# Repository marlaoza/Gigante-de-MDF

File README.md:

```
      _,---.   .=-.-.    _,---.   ,---.      .-._        ,--.--------.    ,----.  
  _.='.'-,  \ /==/_ /_.='.'-,  \.--.'  \    /==/ \  .-._/==/,  -   , -\,-.--` , \ 
 /==.'-     /|==|, |/==.'-     /\==\-/\ \   |==|, \/ /, |==\.-.  - ,-./==|-  _.-` 
/==/ -   .-' |==|  /==/ -   .-' /==/-|_\ |  |==|-  \|  | `--`\==\- \  |==|   `.-. 
|==|_   /_,-.|==|- |==|_   /_,-.\==\,   - \ |==| ,  | -|      \==\_ \/==/_ ,    / 
|==|  , \_.' )==| ,|==|  , \_.' )==/ -   ,| |==| -   _ |      |==|- ||==|    .-'  
\==\-  ,    (|==|- \==\-  ,    (==/-  /\ - \|==|  /\ , |      |==|, ||==|_  ,`-._ 
 /==/ _  ,  //==/. //==/ _  ,  |==\ _.\=\.-'/==/, | |- |      /==/ -//==/ ,     / 
 `--`------' `--`-` `--`------' `--`        `--`./  `--`      `--`--``--`-----``

                     ,----.                ___                  _,---.  
      _,..---._   ,-.--` , \        .-._ .'=.'\  _,..---._   .-`.' ,  \ 
    /==/,   -  \ |==|-  _.-`       /==/ \|==|  /==/,   -  \ /==/_  _.-' 
    |==|   _   _\|==|   `.-.       |==|,|  / - |==|   _   _Y==/-  '..-. 
    |==|  .=.   /==/_ ,    /       |==|  \/  , |==|  .=.   |==|_ ,    / 
    |==|,|   | -|==|    .-'        |==|- ,   _ |==|,|   | -|==|   .--'  
    |==|  '='   /==|_  ,`-._       |==| _ /\   |==|  '='   /==|-  |     
    |==|-,   _`//==/ ,     /       /==/  / / , /==|-,   _`//==/   \     
    `-.`.____.' `--`-----``        `--`./  `--``-.`.____.' `--`---'     
```

O **Gigante de MDF** é um carrinho de batalha controlado por comandos serial via **Bluetooth**, interpretados pelo USART do microcontrolador **ATmega328P**.  

O projeto inclui:
- Dois motores DC 5V controlados por um C.I L298N (movimentação)
- Um sensor **LDR** (detecção de acerto de laser)  
- Um **display de 7 segmentos** (contador de vidas)  
- Um **laser 5 V** (arma)
- Um módulo bluetooth HC-10 (controle)

## Descrição De Recursos

Todas as funcionalidades do carrinho são controladas via bytes enviados pelo HC-10.
Os comandos aceitos são:
| Comando | Ação |
|---------|------|
| `f` | Move o carrinho para frente |
| `b` | Move o carrinho para trás |
| `l` | Vira o carrinho para esquerda |
| `r` | Vira o carrinho para direita |
| `p` | Para os motores |
| `m` | Troca o modo do laser para manual |
| `a` | Troca o modo do laser para automático |
| `s` | Dispara laser (no modo manual) |
| `0` | Girar 180° |
| `1` | Impulso para frente |
| `3` | Reseta vidas |
| `!` | Alterna o modo de depuração |
| `+` / `-` | Ajusta velocidade |
| `h` | Mostra os comandos |

Os motores são controlados pelo C.I de ponte H L298N, com a velocidade sendo modulada via PWM
Cada um dos motores tem um Timer diferente (*Timer0* e *Timer1*) controlando sua saida PWM.

O laser possui dois modos de operação:

### • Modo Automático  
Liga e desliga a cada 1 segundo.

### • Modo Manual  
Controlado por comando Bluetooth.  
Quando ativado, dispara por 1 segundo e entra em *cooldown* por mais 1 segundo.

O tempo do timer é controlado pelo *Timer2* do **Atmega328P** utilizando a interrupção de overflow para contar até 1 segundo

O **LDR** detecta disparos inimigos e remove vidas.  
O display de 7 segmentos exibe o número atual de vidas.

### Modo de Depuração
Quanto ativado, o **Atmega328P** envia para o HC-10 informações extras como os valores lidos pelo LDR e os resultados das interrupções

## Estrutura do Projeto
```bash
/
├── source/
│ └── main.c - Código-fonte em C do firmware
│
├── html/
│ └── Documentação HTML gerada pelo Doxygen
│
├── latex/
│ └── Documentação LaTeX gerada pelo Doxygen
│
├── schematics/
│ ├── schina-ponte-h.kicad_sch - Esquemático do KiCad
│ ├── schina-ponte-h.kicad_pcb -PCB do KiCad
│ └── circSchina.sim1 - Arquivo .simu do SimulIDE
│
└── README.md
```

## Executando no SimulIDE
1. Instale o **SimulIDE** de https://simulide.com/p/
2. Abra o arquivo schematics/circSchina.sim1 com o **SimulIDE**
3. Abra o arquivo source/main.c como código
4. Configure o arquivo como compilador avrgcc
5. Configure o compilador passando o endereço da toolchain do avr-gcc
6. no Device, coloque ATMEGA328P
7. Compile e envie o código para o microcontrolador simulado.

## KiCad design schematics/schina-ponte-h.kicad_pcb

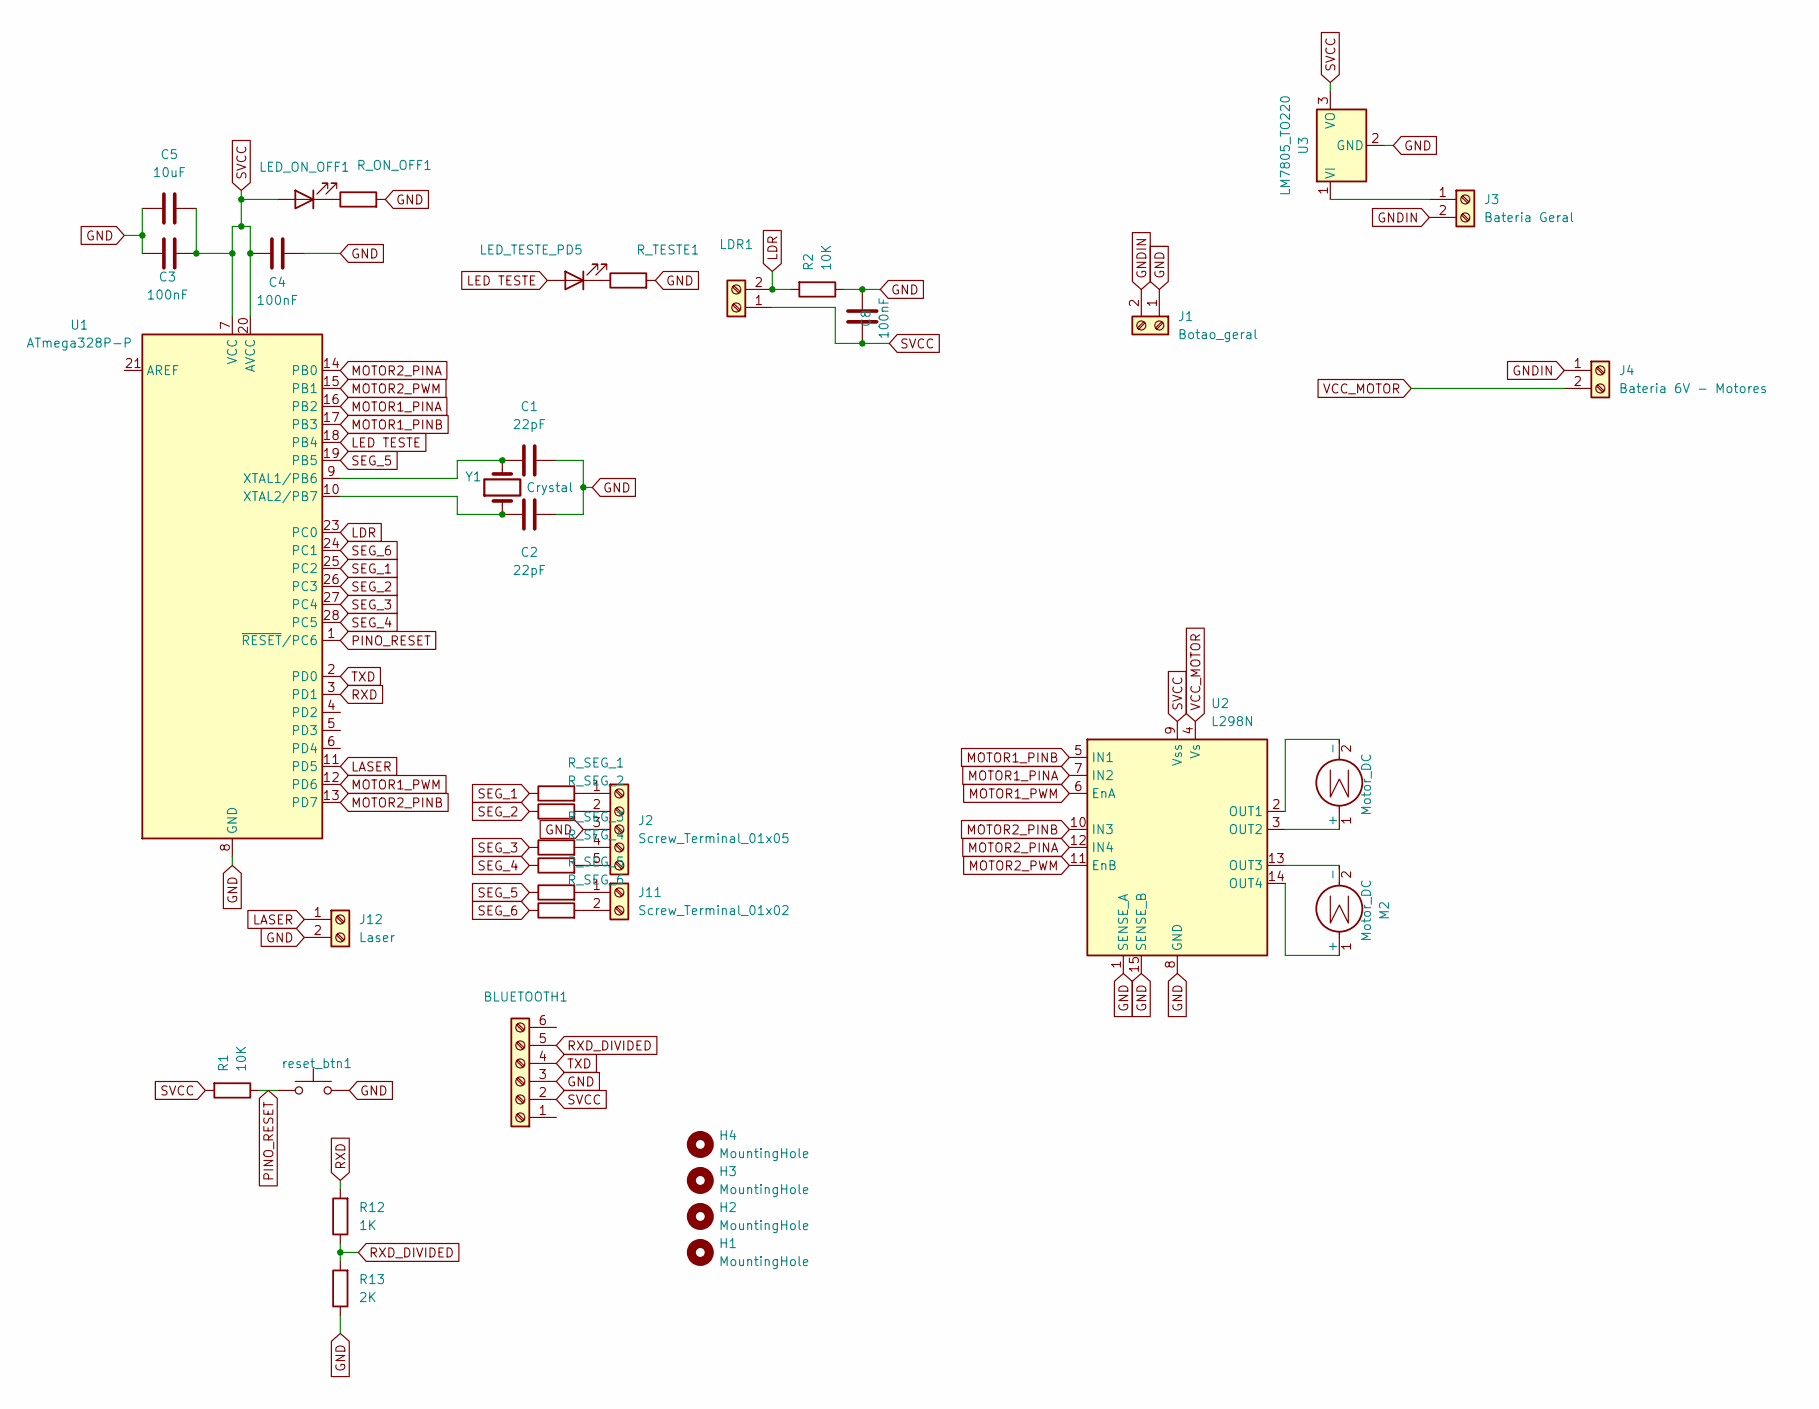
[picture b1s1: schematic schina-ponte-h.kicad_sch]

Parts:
BLUETOOTH1: Screw_Terminal_01x06; PinHeader_1x06_P2.54mm_Vertical
C1, C2: 22pF; CP_Radial_Tantal_D10.5mm_P5.00mm
C3, C4, C8: 100nF; CP_Radial_Tantal_D10.5mm_P5.00mm
C5: 10uF; CP_Radial_D10.0mm_P3.80mm
H1, H2, H3, H4: MountingHole; MountingHole_3.2mm_M3
J1: Botao_geral; TerminalBlock_MaiXu_MX126-5.0-02P_1x02_P5.00mm
J2: Screw_Terminal_01x05; JST_XH_B5B-XH-A_1x05_P2.50mm_Vertical
J3: Bateria Geral; JST_XH_B2B-XH-A_1x02_P2.50mm_Vertical
J4: Bateria 6V - Motores; JST_XH_B2B-XH-A_1x02_P2.50mm_Vertical
J11: Screw_Terminal_01x02; JST_XH_B2B-XH-A_1x02_P2.50mm_Vertical
J12: Laser; JST_XH_B2B-XH-A_1x02_P2.50mm_Vertical
LDR1: JST_XH_B2B-XH-A_1x02_P2.50mm_Vertical
LED_ON_OFF1: LED ARDUINO ON OFF; LED_D3.0mm
LED_TESTE_PD5: LED; LED_D3.0mm
M1, M2: Motor_DC; JST_XH_B2B-XH-A_1x02_P2.50mm_Vertical
R1, R2: 10K; R_Axial_DIN0207_L6.3mm_D2.5mm_P15.24mm_Horizontal
R12: 1K; R_Axial_DIN0207_L6.3mm_D2.5mm_P15.24mm_Horizontal
R13: 2K; R_Axial_DIN0207_L6.3mm_D2.5mm_P15.24mm_Horizontal
R_ON_OFF1: RESISTOR LED ON OFF; R_Axial_DIN0207_L6.3mm_D2.5mm_P15.24mm_Horizontal
R_SEG_1, R_SEG_2, R_SEG_3, R_SEG_4, R_SEG_5, R_SEG_6: RESISTOR LED TESTE; R_Axial_DIN0207_L6.3mm_D2.5mm_P15.24mm_Horizontal
R_TESTE1: RESISTOR LED TESTE; R_Axial_DIN0207_L6.3mm_D2.5mm_P15.24mm_Horizontal
U1: ATmega328P-P; DIP-28_W7.62mm_LongPads
U2: L298N; TO-220-15_P2.54x5.08mm_StaggerOdd_Lead4.58mm_Vertical
U3: LM7805_TO220; TO-220-3_Vertical
Y1: Crystal; Crystal_HC18-U_Vertical
reset_btn1: FREIO EMERGENCIA; SW_PUSH-12mm

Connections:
GND: BLUETOOTH1.3, C1.2, C2.2, C3.1, C4.2, C5.1, C8.2, J1.1, J2.3, J12.2, R2.1, R13.1, R_ON_OFF1.2, R_TESTE1.2, U1.8 (GND), U1.22 (GND), U2.1 (SENSE_A), U2.8 (GND), U2.15 (SENSE_B), U3.2 (GND), reset_btn1.2
GNDIN: J1.2, J3.2, J4.1
LASER: J12.1, U1.11 (PD5)
LDR: LDR1.2, R2.2, U1.23 (PC0)
LED TESTE: LED_TESTE_PD5.2 (A), U1.18 (PB4)
MOTOR1_PINA: U1.16 (PB2), U2.7 (IN2)
MOTOR1_PINB: U1.17 (PB3), U2.5 (IN1)
MOTOR1_PWM: U1.12 (PD6), U2.6 (EnA)
MOTOR2_PINA: U1.14 (PB0), U2.12 (IN4)
MOTOR2_PINB: U1.13 (PD7), U2.10 (IN3)
MOTOR2_PWM: U1.15 (PB1), U2.11 (EnB)
unnamed: J2.1, R_SEG_1.2
unnamed: J2.2, R_SEG_2.2
unnamed: J2.4, R_SEG_3.2
unnamed: J2.5, R_SEG_4.2
unnamed: J3.1, U3.1 (VI)
unnamed: J11.1, R_SEG_5.2
unnamed: J11.2, R_SEG_6.2
unnamed: LED_ON_OFF1.1 (K), R_ON_OFF1.1
unnamed: LED_TESTE_PD5.1 (K), R_TESTE1.1
unnamed: M1.1 (+), U2.3 (OUT2)
unnamed: M1.2 (-), U2.2 (OUT1)
unnamed: M2.1 (+), U2.14 (OUT4)
unnamed: M2.2 (-), U2.13 (OUT3)
unnamed: C1.1, U1.9 (XTAL1/PB6), Y1.2
unnamed: C2.1, U1.10 (XTAL2/PB7), Y1.1
PINO_RESET: R1.1, U1.1 (~RESET/PC6), reset_btn1.1
RXD: R12.2, U1.3 (PD1)
RXD_DIVIDED: BLUETOOTH1.5, R12.1, R13.2
SEG_1: R_SEG_1.1, U1.25 (PC2)
SEG_2: R_SEG_2.1, U1.26 (PC3)
SEG_3: R_SEG_3.1, U1.27 (PC4)
SEG_4: R_SEG_4.1, U1.28 (PC5)
SEG_5: R_SEG_5.1, U1.19 (PB5)
SEG_6: R_SEG_6.1, U1.24 (PC1)
SVCC: BLUETOOTH1.2, C3.2, C4.1, C5.2, C8.1, LDR1.1, LED_ON_OFF1.2 (A), R1.2, U1.7 (VCC), U1.20 (AVCC), U2.9 (Vss), U3.3 (VO)
TXD: BLUETOOTH1.4, U1.2 (PD0)
VCC_MOTOR: J4.2, U2.4 (Vs)

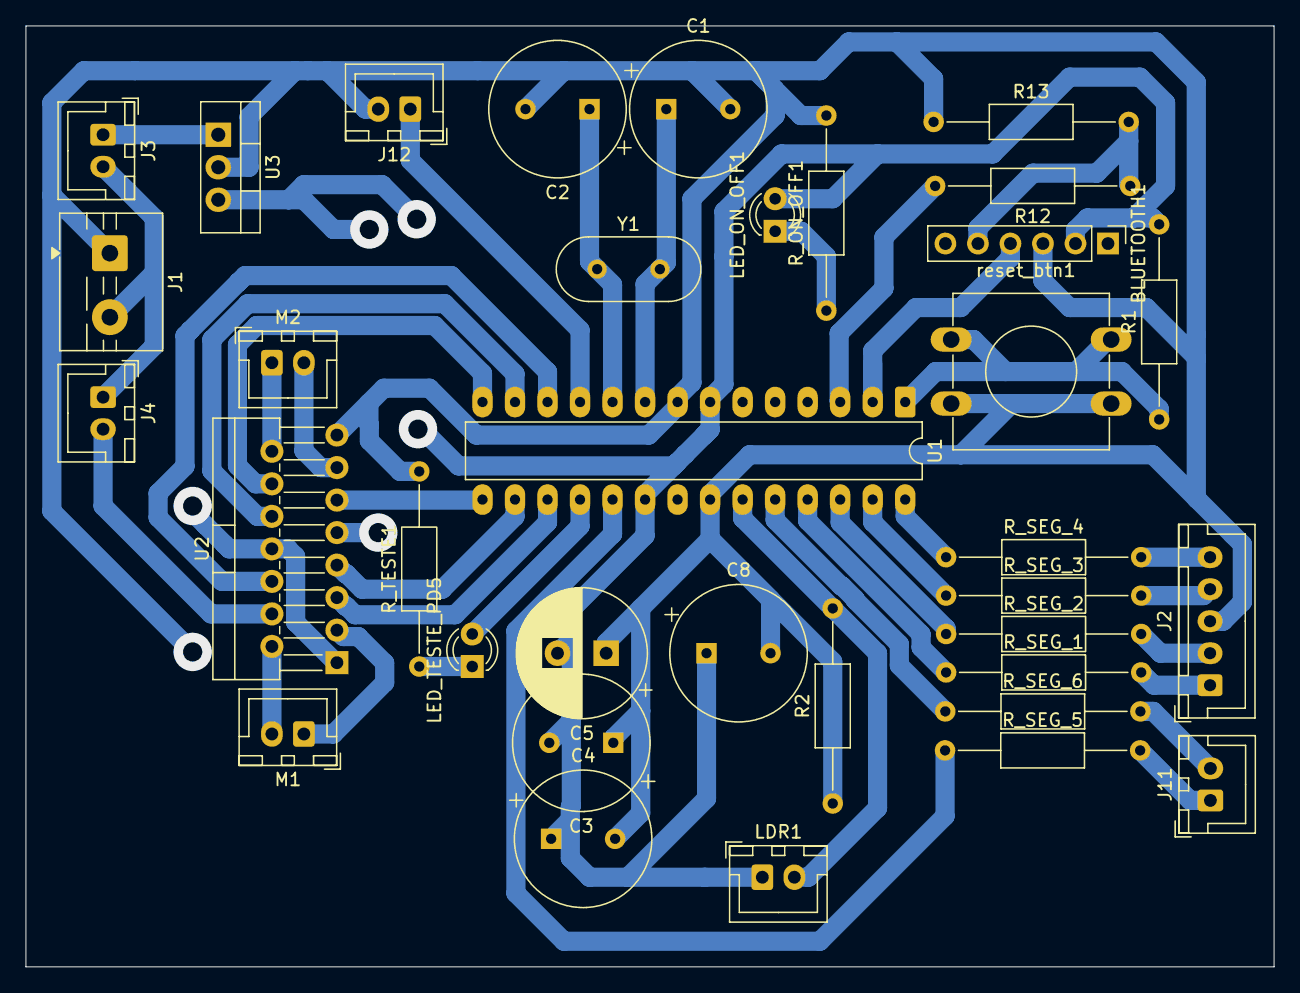
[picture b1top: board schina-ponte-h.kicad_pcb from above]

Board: 2 copper layers, 97.5 x 73.5 mm, 39 parts (0 on the bottom side), 38 nets.

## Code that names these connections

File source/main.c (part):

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
#include <util/delay.h>

#define SEG_A PB5
#define SEG_B PC1
#define SEG_C PC2
#define SEG_D PC3
#define SEG_E PC5
#define SEG_G PC4

#define LDR PC0

#define LASER PD5

#define MOTOR1_A PB2
#define MOTOR1_B PB3
#define MOTOR1_PWM PD6

#define MOTOR2_A PB0
#define MOTOR2_B PD7
#define MOTOR2_PWM PB1

#define TIME_180 200 ///< Tempo necessário para a volta de 180 graus. (em ms)

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
/**
 * Configura e inicializa o PWM com FastPWM
 * Motor 1 - TIMER 0 PORTA A (PD6)
 * Motor 2 - TIMER 1 PORTA A (PB1)
 */ 
void setupMotorsPwm(){
	TCCR0A = (1 << WGM00) | (1 << WGM01) | (1 << COM0A1);   
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	OCR1A = cycle;
}

uint8_t laserCooldown = 0; ///< Flag que determina se o laser esta em cooldown (não pode ser ativado).
uint8_t laserAuto = 1; ///< Flag que controla o modo do motor (1 - AUTO, 2 - MANUAL).

volatile uint16_t laserCounter = 0; ///< Contador de overflows do Timer do Motor
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		if(laserAuto){
			PORTD ^= (1 << LASER);
		}else{	
			if(PIND & (1 << LASER)){
				PORTD &= ~(1 << LASER);
			}else{
				laserCooldown = 0;
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}

/**
 * Aguarda a conversão e retorna a leitura do conversor analógico digital para o pino PC0
 * @return leitura do pino PC0 de 10 bits (0–1023)
 */
uint16_t readLDR() {
    ADMUX = (ADMUX & 0xF0) | 0; 
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	
}

#define LDR_THRESHOLD 900  ///< Valor mínimo de detecção do LDR
char buffer[6]; ///< Buffer 6 bytes para guardar valor lido do LDR convertido para String

/**
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
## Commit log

2025-11-29 FEAT: Initial Files Upload
2025-11-29 FEAT: Help Command
